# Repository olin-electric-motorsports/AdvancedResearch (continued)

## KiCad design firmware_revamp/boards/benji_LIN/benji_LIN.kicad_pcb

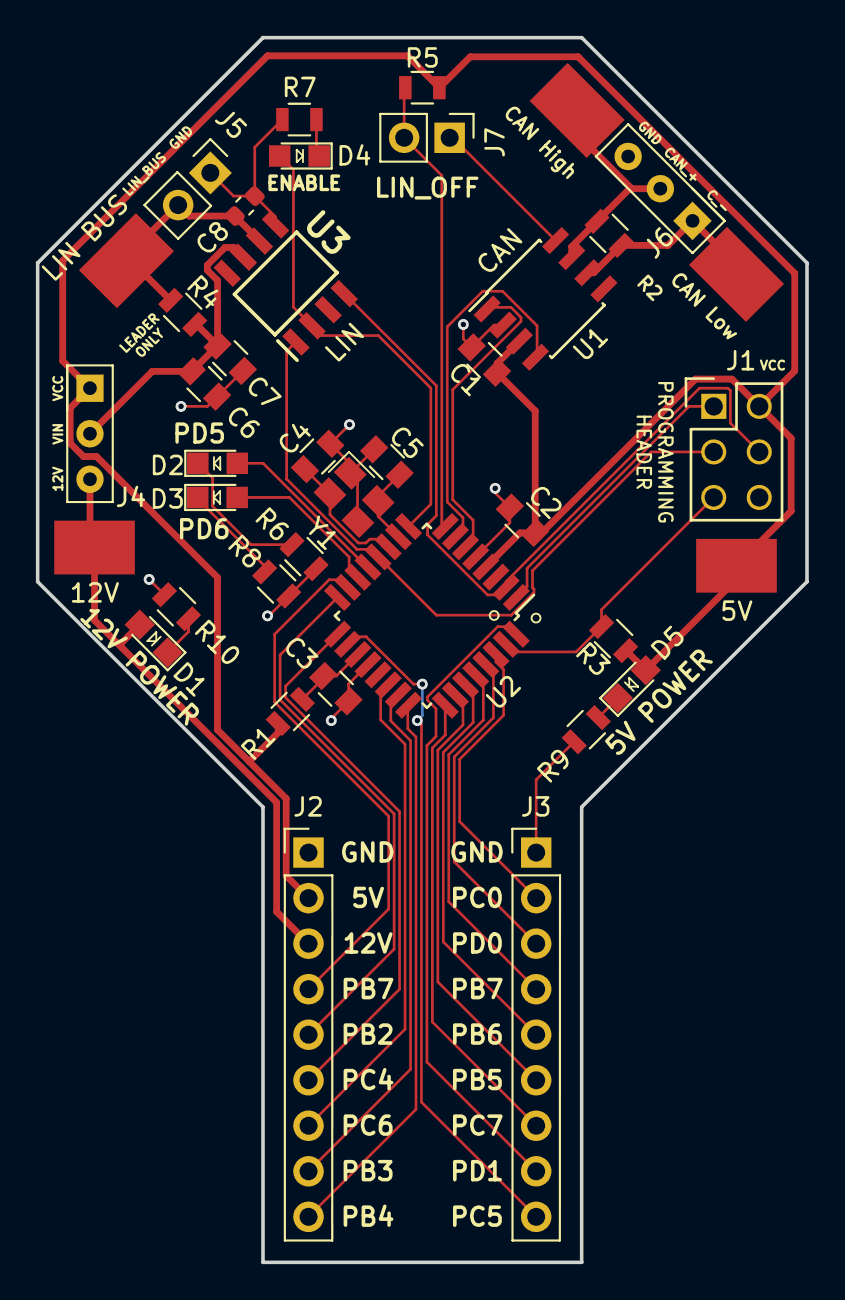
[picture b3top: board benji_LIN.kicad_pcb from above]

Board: 2 copper layers, 42.9 x 68.3 mm, 39 parts (0 on the bottom side), 39 nets.

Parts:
5V, 12V: Test_Point_SMD
C1, C2, C6, C7: C_0.1uF; C_0805_OEM
C3: C_100pF; C_0805_OEM
C4, C5: C_30pF; C_0805_OEM
C8: C_220pF; C_0603_1608Metric
CAN High: Test_Point_SMD
CAN Low: Test_Point_SMD
D1, D5: LED_0805_Amber; LED_0805_OEM
D2: LED_0805; LED_0805_OEM
D3: LED_0805_Red; LED_0805_OEM
D4: LIN_INDICATOR_LED; LED_0805_OEM
J1: CONN_02X03; Pin_Header_Straight_2x03
J2, J3: Conn_01x09; PinHeader_1x9_P2.54mm_Vertical
J4, J6: CONN_01X03; PinHeader_1x03_P2.54mm_Vertical
J5, J7: CONN_01x02; PinHeader_1x02_P2.54mm_Vertical
LIN BUS: Test_Point_SMD
R1: R_100; R_0805_OEM
R2: R_120_DNP; R_0805_OEM
R3: R_10K; R_0805_OEM
R4, R5, R6, R7, R8, R9: R_1K; R_0805_OEM
R10: R_2.2K; R_0805_OEM
U1: MCP2561-E_SN; SOIC-8_3.9x4.9mm_Pitch1.27mm_OEM
U2: ATMEGA16M1; TQFP-32_7x7mm_Pitch0.8mm
U3: TLIN1021DRQ1; SOIC127P600X175-8N
Y1: Crystal_SMD; Crystal_SMD_FA238

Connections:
/12V: 12V.1, D1.2, J2.3, J4.3
/CAN_+: CAN High.1, J6.2, R2.1, U1.7
/CAN_-: CAN Low.1, J6.1, R2.2, U1.6
/CAN_RX: U1.4, U2.7
/CAN_TX: U1.1, U2.6
/ENABLE: D4.2, U2.9, U3.2
/LEFT_DEBUG: D2.2, U2.13
/LIN_BUS: C8.1, J5.2, LIN BUS.1, R4.2, U3.6
/MISO: J1.1, U2.1
/MOSI: J1.4, U2.2, U3.4
/PB2: J2.5, U2.16
/PB3: J2.8, U2.23
/PB4: J2.9, U2.24
/PB5: J3.6, U2.26
/PB6: J3.5, U2.27
/PB7: J3.4, U2.28
/PC0: J3.2, U2.30
/PC4: J2.6, U2.17
/PC5: J3.9, U2.18
/PC6: J2.7, U2.22
/PC7: J3.7, U2.25
/PD0: J3.3, U2.29
/PD1: J3.8, U2.32
/PD7: J2.4, U2.15
/RESET: J1.5, R3.2, U2.31
/RIGHT_DEBUG: D3.2, U2.14
/RXLIN: J1.3, U2.12, U3.1
/VIN: C6.1, C7.1, J4.2, R4.1, U3.7
GND: C1.2, C2.2, C3.2, C4.2, C5.2, C6.2, C7.2, C8.2, J1.6, J2.1, J3.1, J5.1, J6.3, J7.1, R6.2, R7.2, R8.2, R9.2, R10.2, U1.2, U1.8, U2.5, U2.20, U3.5, Y1.2, Y1.4
unnamed: C3.1, R1.2, U2.19
unnamed: C4.1, U2.11, Y1.1
unnamed: C5.1, U2.10, Y1.3
unnamed: D1.1, R10.1
unnamed: D2.1, R6.1
unnamed: D3.1, R8.1
unnamed: D4.1, R7.1
unnamed: D5.1, R9.1
unnamed: J7.2, R5.1, U2.8
VCC: 5V.1, C1.1, C2.1, D5.2, J1.2, J2.2, J4.1, R1.1, R3.1, R5.2, U1.3, U2.4

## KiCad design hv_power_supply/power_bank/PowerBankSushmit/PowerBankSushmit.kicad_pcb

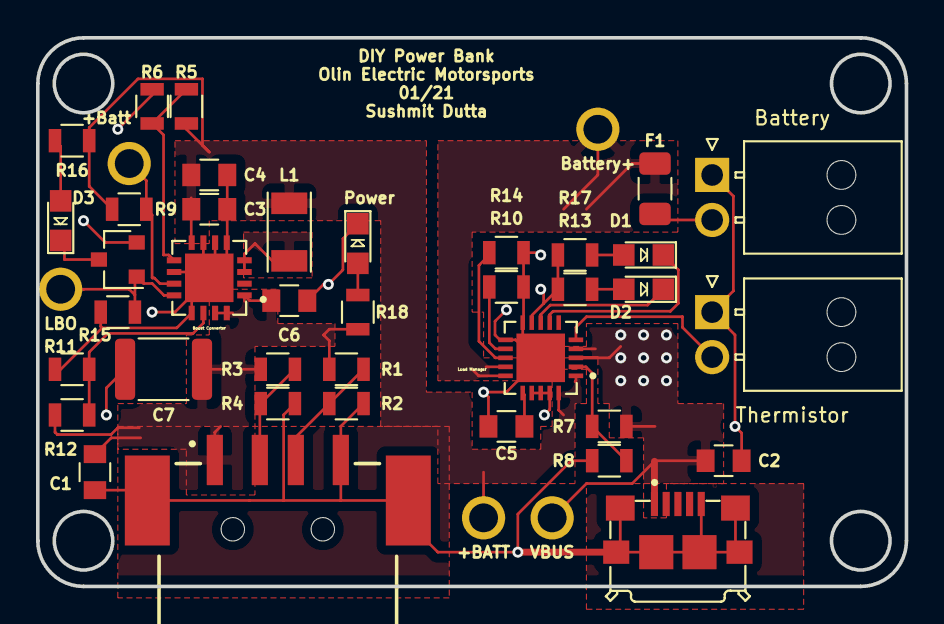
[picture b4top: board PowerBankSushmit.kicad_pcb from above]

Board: 2 copper layers, 48.3 x 30.5 mm, 43 parts (0 on the bottom side), 25 nets.

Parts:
+BATT: TP; tp_1.6mm
+Batt: TP; tp_1.6mm
Battery: NanoFit_RA_TH_02; NanoFit_Molex_1x02x2.50mm_Angled_OEM
Battery+: TP; tp_1.6mm
Boost Converter: TPS61090RSAR
C1, C2, C3, C4: C_10uF; C_0805_OEM
C5: C_10nF; C_0805_OEM
C6: C_2.2uF; C_0805_OEM
C7: C_100uF; C_1812_4532Metric
D1, D3: LED_0805; LED_0805_OEM
D2: LED_0805_Amber; LED_0805_OEM
F1: 1.5A_Fuse; Fuse_1206
J3: USB-A-S-X-X-SM2; SAMTEC_USB-A-S-X-X-SM2
L1: L_6.8uH; L_100uH_OEM
LBO: TP; tp_1.6mm
Load Manager: MCP73871T-2CCI_ML; MCP73871T
Power : LED_0805; LED_0805_OEM
Q1: SSM3K333R; SOT-23F
R1: R_75k; R_0805_OEM
R2, R4: R_49.9K; R_0805_OEM
R3: R_43k; R_0805_OEM
R5, R11: R_1.87M; R_0805_OEM
R6: R_340K; R_0805_OEM
R7: R_270K; R_0805_OEM
R8, R10: R_100K; R_0805_OEM
R9, R12: R_200K; R_0805_OEM
R13, R14, R16, R17, R18: R_1K; R_0805_OEM
R15: R_10K; R_0805_OEM
Thermistor: NanoFit_RA_TH_02; NanoFit_Molex_1x02x2.50mm_Angled_OEM
U1: USB-Micro-1981568-1; TE_1981568-1
VBUS: TP; tp_1.6mm

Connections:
+5V: Boost Converter.1, Boost Converter.15, Boost Converter.16, C1.1, C6.1, C7.1, J3.01, R1.1, R3.1, R11.1, R18.1
+BATT: +BATT.1, Boost Converter.8, C3.1, C4.1, L1.1, Load Manager.1, Load Manager.20, R5.1, R9.2, R16.1
/16K_Thermistor: Load Manager.5, Thermistor.2
/Battery+: Battery+.1, F1.2, Load Manager.14, Load Manager.15
GND: Battery.1, Boost Converter.5, Boost Converter.6, Boost Converter.7, Boost Converter.10, Boost Converter.13, Boost Converter.17, C1.2, C2.2, C3.2, C4.2, C5.2, C6.2, C7.2, J3.04, J3.S1, J3.S2, Load Manager.10, Load Manager.11, Load Manager.21, Power.1, Q1.2, R2.2, R4.2, R6.2, R8.2, R10.2, R12.2, R14.2, R15.2, Thermistor.1, U1.5, U1.6, U1.7, U1.8, U1.9, U1.10, U1.11
unnamed: C5.1, Load Manager.16
unnamed: D1.1, Load Manager.7
unnamed: D1.2, R17.1
unnamed: D2.1, Load Manager.8
unnamed: D2.2, R13.2
unnamed: D3.1, Q1.3
unnamed: D3.2, R16.2
unnamed: Power.2, R18.2
unnamed: Battery.2, F1.1
unnamed: J3.02, R3.2, R4.1
unnamed: J3.03, R1.2, R2.1
unnamed: Boost Converter.3, Boost Converter.4, L1.2
unnamed: Boost Converter.12, LBO.1, Q1.1, R15.1
unnamed: Boost Converter.9, R5.2, R6.1
unnamed: Load Manager.2, R7.2, R8.1
unnamed: +Batt.1, Boost Converter.11, R9.1
unnamed: Load Manager.12, R10.1
unnamed: Boost Converter.14, R11.2, R12.1
unnamed: Load Manager.13, R14.1
VBUS: C2.1, Load Manager.3, Load Manager.4, Load Manager.9, Load Manager.17, Load Manager.18, Load Manager.19, R7.1, R13.1, R17.2, U1.1, VBUS.1

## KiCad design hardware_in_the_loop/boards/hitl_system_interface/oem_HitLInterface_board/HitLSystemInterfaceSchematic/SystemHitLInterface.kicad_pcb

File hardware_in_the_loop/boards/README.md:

# Boards

This is where the KiCAD files for the Hardware in the Loop project live.

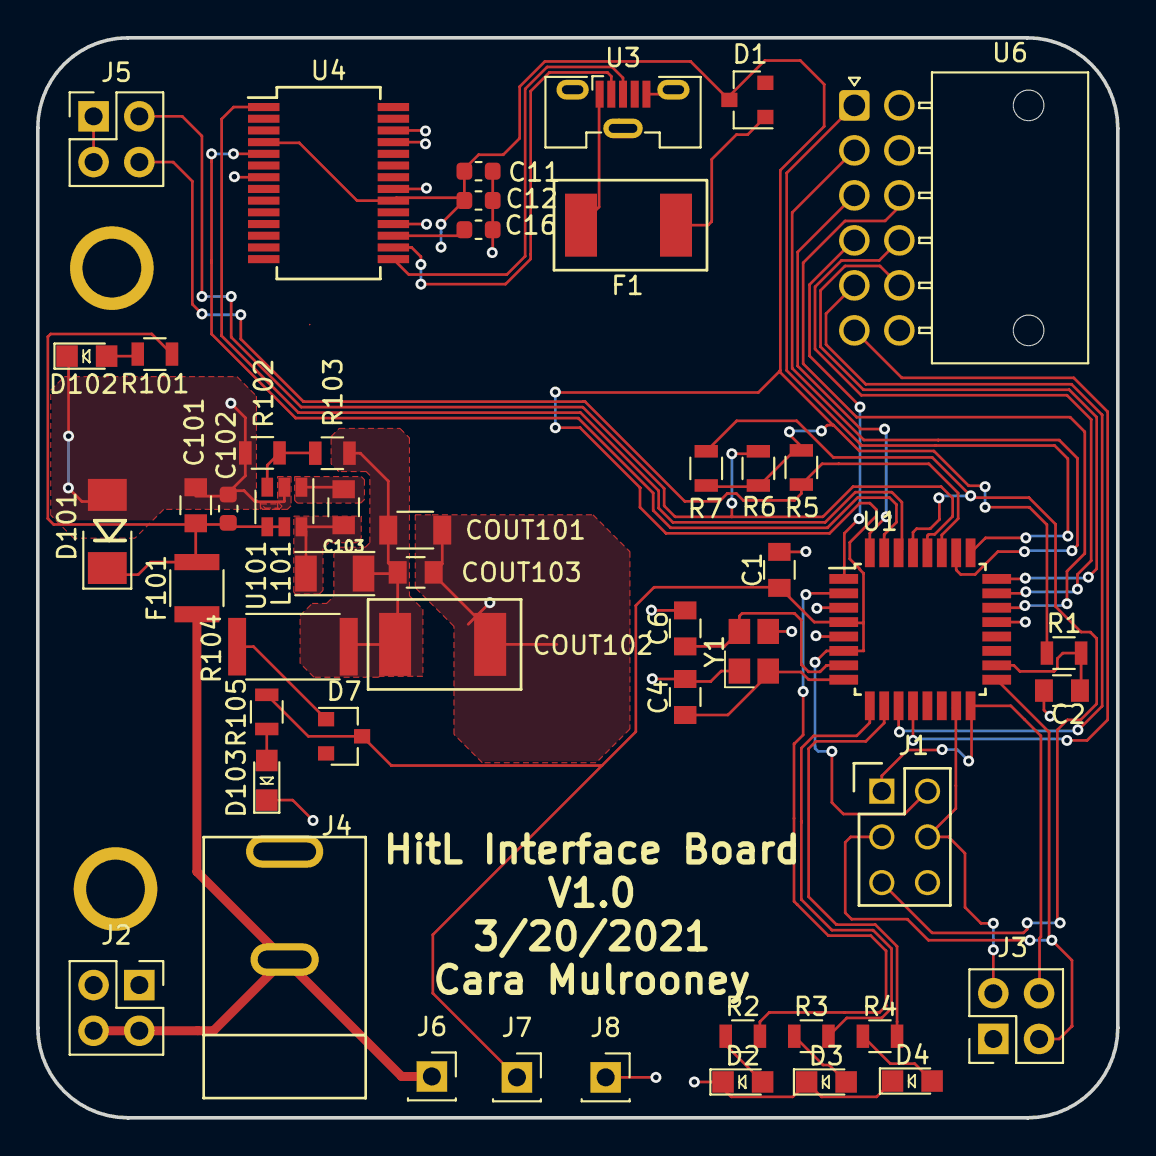
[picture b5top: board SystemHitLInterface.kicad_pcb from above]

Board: 2 copper layers, 60.0 x 60.0 mm, 50 parts (0 on the bottom side), 42 nets.

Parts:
C1, C101, C103: C_0.1uF; C_0805_OEM
C2: C_100pF; C_0805_OEM
C4, C6: C_30pF; C_0805_OEM
C11: C_4.7uF; C_0603_1608Metric
C12, C16: C_100nF; C_0603_1608Metric
C102: C_2.2uF; C_0603_1608Metric
COUT101: C_22uF; C_1206_OEM
COUT102: C_33uF; Fuse_1812
COUT103: C_47uF; C_0805_OEM
D1, D7: BAS40-00; SOT-23
D2, D3, D4, D102, D103: LED_0805; LED_0805_OEM
D101: D_Zener_18V; DO-214AA
F1: 200mA_Fuse; Fuse_1812
F101: F_500mA_16V; Fuse_1210
J1: CONN_02X03; Pin_Header_Straight_2x03
J2, J3, J5: Conn_01x04_Female; PinSocket_2x02_P2.54mm_Vertical
J4: Barrel_Jack; barrel_jack_PJ-037A
J6, J7, J8: Conn_01x01_Female; PinSocket_1x01_P2.54mm_Vertical
L101: L_100uH; L_100uH_OEM
R1: R_100; R_0805_OEM
R2, R3, R4, R105: R_200; R_0805_OEM
R5, R6, R7: R_10K; R_0805_OEM
R101: R_1K; R_0805_OEM
R102: R_25K; R_0805_OEM
R103: R_100K; R_0805_OEM
R104: R_0_2512; R_2512_OEM
U1: ATmega328P-AU; TQFP-32_7x7mm_P0.8mm
U3: USB_MicroB; USB_Micro-B_Molex-105133-0031
U4: FT232RL; SSOP-28_5.3x10.2mm_P0.65mm
U6: NanoFit_RA_TH_12; NanoFit_RA_12
U101: TPS560430YF; SOT-23-6_OEM
Y1: Crystal_SMD; Crystal_SMD_FA238

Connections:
/12V: F101.1, J2.3, J2.4, J4.2, J6.1
/AI2: U1.22, U6.9
/AI3: U1.23, U6.10
/AI4: U1.24, U6.11
/D1: U1.25, U6.1
/D2: U1.26, U6.2
/D3: U1.32, U6.3
/D4: U1.1, U6.4
/D5: U1.11, U6.5
/D6: U1.12, U6.6
/MISO: J1.1, J3.4, U1.16
/MOSI: J1.4, J3.3, U1.15
/RESET: J1.5, R7.2, U1.29
/RXD: U1.30, U4.1
/SCK: J1.3, J3.2, U1.17
/SCL: J5.3, R6.2, U1.28
/SDA: J5.4, R5.2, U1.27
/TXD: U1.31, U4.5
/USBDM: U3.2, U4.16
/USBDP: U3.3, U4.15
GND: C1.2, C2.2, C4.2, C6.2, C11.1, C12.1, C16.2, C101.2, C102.2, COUT101.2, COUT102.2, COUT103.2, D2.1, D3.1, D4.1, D101.2, D102.1, D103.1, J1.6, J2.1, J2.2, J4.1, J5.1, J5.2, J8.1, R102.2, U1.3, U1.5, U1.21, U3.5, U3.6, U4.7, U4.18, U4.21, U4.25, U4.26, U101.2, Y1.2, Y1.4
unnamed: C2.1, R1.2, U1.18
unnamed: C4.1, U1.8, Y1.1
unnamed: C6.1, U1.7, Y1.3
unnamed: C16.1, U4.17
unnamed: C101.1, C102.1, D101.1, F101.2, R101.1, U101.4, U101.5
unnamed: C103.1, U101.1
unnamed: C103.2, L101.1, U101.6
unnamed: COUT101.1, COUT102.1, COUT103.1, L101.2, R103.1, R104.1
unnamed: D1.1, F1.2
unnamed: D2.2, R2.1
unnamed: D3.2, R3.1
unnamed: D4.2, R4.1
unnamed: D7.1, R104.2
unnamed: D102.2, R101.2
unnamed: D103.2, R105.2
unnamed: F1.1, U3.1
unnamed: R2.2, U1.2
unnamed: R3.2, U1.9
unnamed: R4.2, U1.10
unnamed: R102.1, R103.2, U101.3
VCC: C1.1, C11.2, C12.2, D1.3, D7.3, J1.2, J7.1, R1.1, R5.1, R6.1, R7.1, R105.1, U1.4, U1.6, U4.4, U4.20

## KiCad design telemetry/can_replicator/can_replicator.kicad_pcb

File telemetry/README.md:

# Telemetry

This project will allow wireless communication between the car's communications bus and the pit.

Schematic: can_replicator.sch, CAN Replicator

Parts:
C1, C2: C_0.1uF; C_0805_OEM; MPN 478-3352-1-ND
C3: C_100pF; C_0805_OEM; MPN 732-7852-1-ND
C4, C5: C_30pF; C_0805_OEM; MPN 1276-1130-1-ND
C6: C_10nF; C_0805_OEM; MPN 1276-1015-1-ND
C7, C9: C_100nF; C_0603_1608Metric; MPN 1276-6717-1-ND
C8: C_4.7uF; C_0603_1608Metric; MPN 1276-1045-1-ND
D1, D2: LED_0805_Amber; LED_0805_OEM; MPN L71517CT-ND
D3, D4, D5, D6: LED_0805; LED_0805_OEM; MPN 475-1410-1-ND
D7: BAT400D-7-F; SOT-23-3_OEM
D8: D_Zener_5.6V; D_5.6V_Zener; MPN 3SMBJ5919B-TP
F1: F_500mA_16V; Fuse_1210; MPN 507-1786-1-ND
J1: CONN_02X03; Pin_Header_Straight_2x03; MPN 609-3234-ND
J2: MM_M_VT_20; micromatch_female_ra_20; MPN 2-215464-0
J3, J4: CONN_01X03; PinHeader_1x03_P2.54mm_Vertical; MPN 855-M20-9990346
R1: R_100; R_0805_OEM; MPN RNCP0805FTD100RCT-ND
R2, R12: R_120; R_0805_OEM; MPN 667-ERJ-6ENF1200V
R3: R_10K; R_0805_OEM; MPN CRS0805-FX-1002ELFCT-ND
R4, R5, R6, R7, R8, R9: R_200; R_0805_OEM; MPN RMCF0805JT200RCT-ND
R10, R11: R_500; R_0805_OEM
TP1, TP2: Test_Point_SMD
U1: MCP2561-E_SN; SOIC-8_3.9x4.9mm_Pitch1.27mm_OEM; MPN MCP2561-E/SN-ND
U2: ATMEGA16M1; TQFP-32_7x7mm_Pitch0.8mm; MPN ATMEGA16M1-AU-ND
U3: USB_MicroB; USB_Micro-B_Molex-105017-0001; MPN WM1399CT-ND
U4: FT232RL; SSOP-28_5.3x10.2mm_P0.65mm; Part Number (DK) 768-1007-1-ND
Y1: Crystal_SMD; Crystal_SMD_FA238; MPN 887-1125-1-ND

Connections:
+5V: C1.1, C2.1, C6.2, C7.1, C8.1, D1.2 (A), D2.2 (A), D3.2 (A), D7.1 (K), D8.1 (K), J1.2, R1.1, R3.1, U1.3 (VDD), U2.4 (VCC), U4.4 (VCCIO), U4.19 (~RESET~), U4.20 (VCC)
/CAN_+: J2.3, R2.1, R12.1, U1.7 (CANH)
/CAN_-: J2.4, J3.2, J4.2, U1.6 (CANL)
/CAN_RX: U1.4 (RXD), U2.7 ((PCINT11/T1/ICP1B/RXCAN)PC3)
/CAN_TX: U1.1 (TXD), U2.6 ((PCINT10/T0/TXCAN)PC2)
/DBG1: D4.2 (A), U2.22 ((PCINT14/ADC10/ACMP1)PC6)
/DBG2: D5.2 (A), U2.23 ((PCINT3/AMP0-)PB3)
/DBG3: D6.2 (A), U2.24 ((PCINT4/AMP0+)PB4)
/MISO: J1.1, U2.1 ((PCINT18/PSCIN2/OC1A/MISO_A)PD2)
/MOSI: J1.4, R10.1, U2.2 ((PCINT19/TXD/TXLIN/OC0A/~SS~/MOSI_A)PD3)
/RESET: J1.5, R3.2, U2.31 ((PCINT24/OCD/~RESET~)PE0)
/RXLED: R7.1, U4.22 (CBUS1)
/SCK: J1.3, R11.1, U2.12 ((PCINT20/ADC1/RXD/RXLIN/ICP1A/SCK_A)PD4)
/TXLED: R8.1, U4.23 (CBUS0)
/UART_RXD: R10.2, U4.5 (RXD)
/UART_TXD: R11.2, U4.1 (TXD)
/USBD+: U3.3 (D+), U4.15 (USBD+)
/USBD-: U3.2 (D-), U4.16 (USBD-)
GND: C1.2, C2.2, C3.2, C4.2, C5.2, C6.1, C7.2, C8.2, C9.2, D8.2 (A), J1.6, J2.1, J2.5, J2.6, J2.7, J2.8, J2.9, J2.10, J2.11, J2.12, J2.13, J2.14, J2.15, J2.16, J2.17, J2.18, J2.19, J2.20, R4.1, R5.1, R6.1, R9.1, TP1.1, U1.2 (VSS), U1.8 (STBY), U2.5 (GND), U2.20 (AGND), U3.5 (GND), U4.7 (GND), U4.18 (GND), U4.21 (GND), U4.25 (AGND), U4.26 (TEST), Y1.2, Y1.4
unnamed: C3.1, R1.2, U2.19 (AVCC)
unnamed: C4.1, U2.11 ((PCINT26/ADC0/XTAL2)PE2), Y1.1
unnamed: C5.1, U2.10 ((PCINT25/OC0B/XTAL1)PE1), Y1.3
unnamed: C9.1, U4.17 (3V3OUT)
unnamed: D1.1 (K), R7.2
unnamed: D2.1 (K), R8.2
unnamed: D3.1 (K), R9.2
unnamed: D4.1 (K), R4.2
unnamed: D5.1 (K), R5.2
unnamed: D6.1 (K), R6.2
unnamed: D7.2 (A), F1.1
unnamed: F1.2, TP2.1, U3.1 (VBUS)
unnamed: J3.3, R2.2
unnamed: J4.3, R12.2

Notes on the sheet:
ATMEGA 16M1
16 MHz CRYSTAL
USB + POWER
+4.4V - +5.25V
USB RX
USB TX
POWER
STATUS LEDS
CAN TRANSCEIVER
CONNECTOR
16M1 PROGRAMMING HEADER
JUMPERS FOR TERMINATING RESISTORS

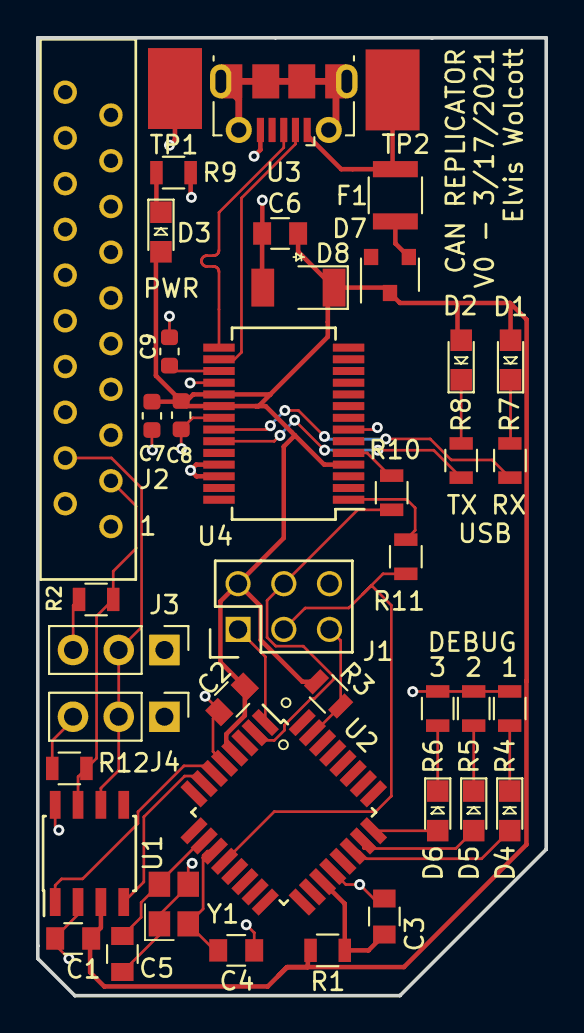
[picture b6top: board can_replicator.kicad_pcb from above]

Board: 2 copper layers, 28.2 x 53.2 mm, 41 parts (0 on the bottom side), 33 nets.

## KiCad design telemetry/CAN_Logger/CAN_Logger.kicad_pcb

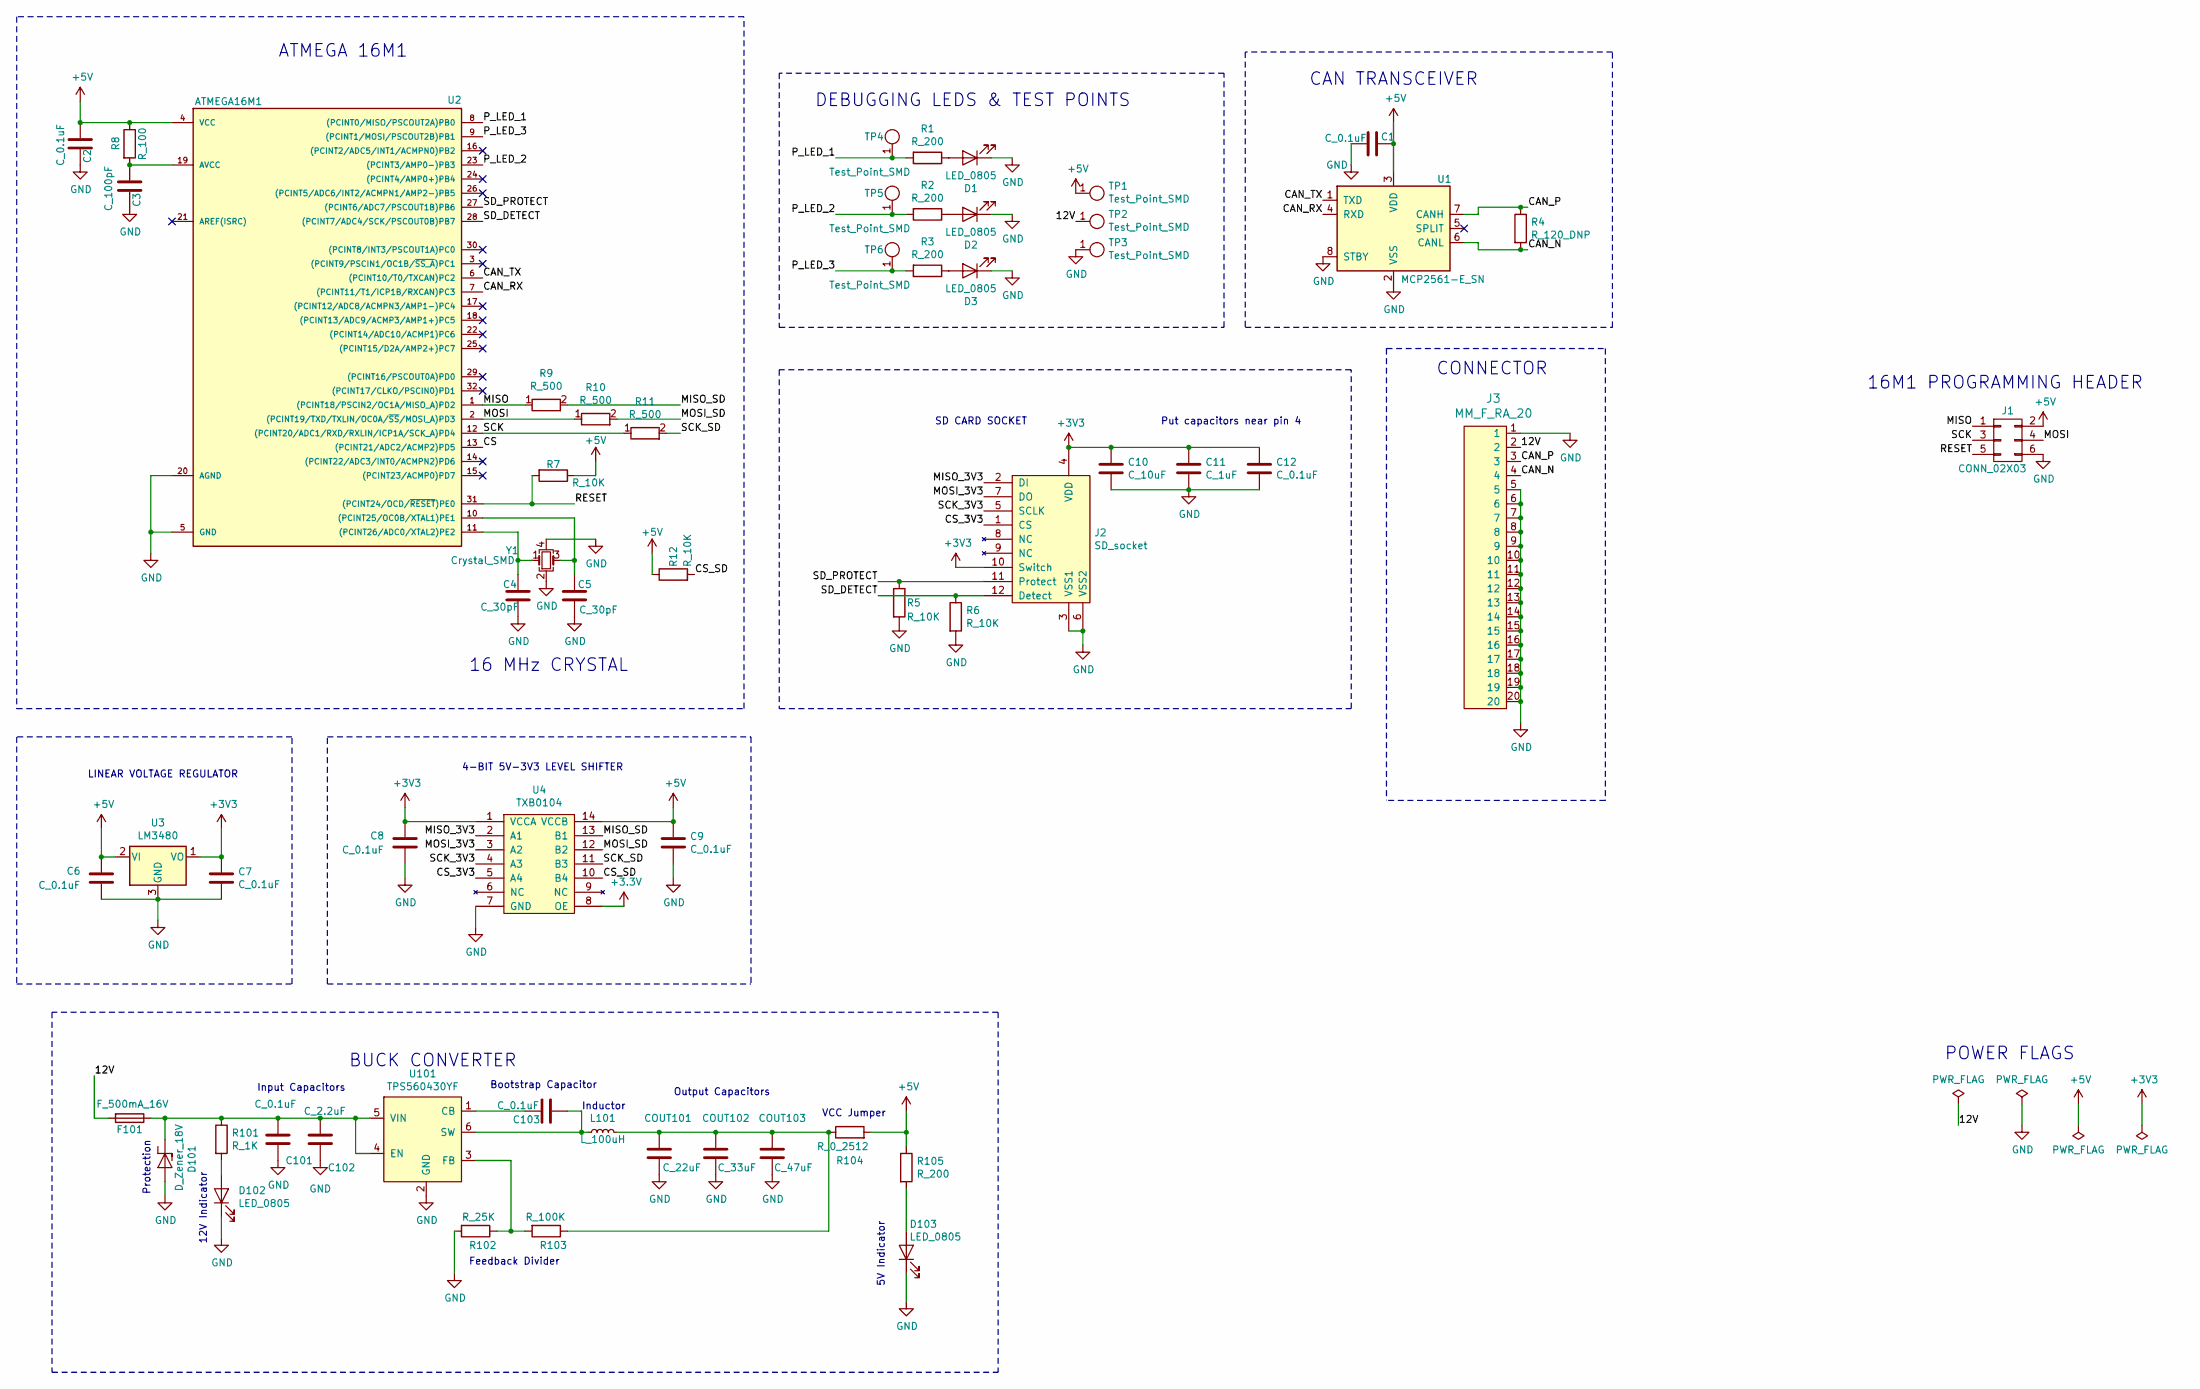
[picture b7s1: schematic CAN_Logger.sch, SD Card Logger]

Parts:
C1, C2, C6, C7, C8, C9, C12, C101, C103: C_0.1uF; C_0805_OEM; MPN 478-3352-1-ND
C3: C_100pF; C_0805_OEM; MPN 732-7852-1-ND
C4, C5: C_30pF; C_0805_OEM; MPN 1276-1130-1-ND
C10: C_10uF; C_0805_OEM; MPN 1276-1052-1-ND
C11: C_1uF; C_0805_OEM
C102: C_2.2uF; C_0603_1608Metric
COUT101: C_22uF; C_1206_OEM; MPN 445-11693-1-ND
COUT102: C_33uF; Fuse_1812; MPN 445-3924-1-ND
COUT103: C_47uF; C_0805_OEM; MPN 1276-6467-1-ND
D1, D2, D3, D102, D103: LED_0805; LED_0805_OEM; MPN 475-1410-1-ND
D101: D_Zener_18V; DO-214AA; MPN SMBJ5355B-TPMSCT-ND
F101: F_500mA_16V; Fuse_1210; MPN 507-1786-1-ND
J1: CONN_02X03; Pin_Header_Straight_2x03; MPN 609-3234-ND
J2: SD_socket; sd_socket_molex_5009980900; MPN WM24032CT-ND
J3: MM_F_RA_20; micromatch_female_ra_20; MPN 2-338070-0
L101: L_100uH; L_100uH_OEM; MPN 445-15759-1-ND
R1, R2, R3, R105: R_200; R_0805_OEM; MPN RMCF0805JT200RCT-ND
R4: R_120_DNP; R_0805_OEM; MPN 667-ERJ-6ENF1200V
R5, R6, R7, R12: R_10K; R_0805_OEM; MPN CRS0805-FX-1002ELFCT-ND
R8: R_100; R_0805_OEM; MPN RNCP0805FTD100RCT-ND
R9, R10, R11: R_500; R_0805_OEM
R101: R_1K; R_0805_OEM; MPN RNCP0805FTD1K00CT-ND
R102: R_25K; R_0805_OEM; MPN A124124CT-ND
R103: R_100K; R_0805_OEM; MPN P100KCCT-ND
R104: R_0_2512; R_2512_OEM; MPN A121322CT-ND
TP1, TP2, TP3, TP4, TP5, TP6: Test_Point_SMD
U1: MCP2561-E_SN; SOIC-8_3.9x4.9mm_Pitch1.27mm_OEM; MPN MCP2561-E/SN-ND
U2: ATMEGA16M1; TQFP-32_7x7mm_Pitch0.8mm; MPN ATMEGA16M1-AU-ND
U3: LM3480; SOT-23; MPN LM3480IM3-3.3CT-ND
U4: TXB0104; TSSOP-14_4.4x5mm_P0.65mm; MPN 296-21929-1-ND
U101: TPS560430YF; SOT-23-6_OEM; MPN TPS560430YFDBVR-ND
Y1: Crystal_SMD; Crystal_SMD_FA238; MPN 887-1125-1-ND

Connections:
+5V: C1.1, C2.1, C6.1, C9.1, J1.2, R7.1, R8.1, R12.1, R104.2, R105.1, TP1.1, U1.3 (VDD), U2.4 (VCC), U3.2 (VI), U4.14 (VCCB)
/12V: F101.2, J3.2, TP2.1
/CAN_N: J3.4, R4.2, U1.6 (CANL)
/CAN_P: J3.3, R4.1, U1.7 (CANH)
/CAN_RX: U1.4 (RXD), U2.7 ((PCINT11/T1/ICP1B/RXCAN)PC3)
/CAN_TX: U1.1 (TXD), U2.6 ((PCINT10/T0/TXCAN)PC2)
/CS_3V3: J2.1 (CS), U4.5 (A4)
/MISO: J1.1, R9.1, U2.1 ((PCINT18/PSCIN2/OC1A/MISO_A)PD2)
/MISO_3V3: J2.2 (DI), U4.2 (A1)
/MISO_SD: R9.2, U4.13 (B1)
/MOSI: J1.4, R10.1, U2.2 ((PCINT19/TXD/TXLIN/OC0A/~SS~/MOSI_A)PD3)
/MOSI_3V3: J2.7 (DO), U4.3 (A2)
/MOSI_SD: R10.2, U4.12 (B2)
/P_LED_1: R1.2, TP4.1, U2.8 ((PCINT0/MISO/PSCOUT2A)PB0)
/P_LED_2: R2.2, TP5.1, U2.23 ((PCINT3/AMP0-)PB3)
/P_LED_3: R3.2, TP6.1, U2.9 ((PCINT1/MOSI/PSCOUT2B)PB1)
/RESET: J1.5, R7.2, U2.31 ((PCINT24/OCD/~RESET~)PE0)
/SCK: J1.3, R11.1, U2.12 ((PCINT20/ADC1/RXD/RXLIN/ICP1A/SCK_A)PD4)
/SCK_3V3: J2.5 (SCLK), U4.4 (A3)
/SCK_SD: R11.2, U4.11 (B3)
/SD_DETECT: J2.12 (Detect), R6.1, U2.28 ((PCINT7/ADC4/SCK/PSCOUT0B)PB7)
/SD_PROTECT: J2.11 (Protect), R5.1, U2.27 ((PCINT6/ADC7/PSCOUT1B)PB6)
GND: C1.2, C2.2, C3.2, C4.2, C5.2, C6.2, C7.2, C8.2, C9.2, C10.2, C11.2, C12.2, C101.2, C102.2, COUT101.2, COUT102.2, COUT103.2, D1.1 (K), D2.1 (K), D3.1 (K), D101.2 (A), D102.1 (K), D103.1 (K), J1.6, J2.3 (VSS1), J2.6 (VSS2), J3.1, J3.5, J3.6, J3.7, J3.8, J3.9, J3.10, J3.11, J3.12, J3.13, J3.14, J3.15, J3.16, J3.17, J3.18, J3.19, J3.20, R5.2, R6.2, R102.2, TP3.1, U1.2 (VSS), U1.8 (STBY), U2.5 (GND), U2.20 (AGND), U3.3 (GND), U4.7 (GND), U101.2 (GND), Y1.2, Y1.4
unnamed: C3.1, R8.2, U2.19 (AVCC)
unnamed: C4.1, U2.11 ((PCINT26/ADC0/XTAL2)PE2), Y1.1
unnamed: C5.1, U2.10 ((PCINT25/OC0B/XTAL1)PE1), Y1.3
unnamed: C101.1, C102.1, D101.1 (K), F101.1, R101.1, U101.4 (EN), U101.5 (VIN)
unnamed: C103.1, U101.1 (CB)
unnamed: C103.2, L101.1, U101.6 (SW)
unnamed: COUT101.1, COUT102.1, COUT103.1, L101.2, R103.1, R104.1
unnamed: D1.2 (A), R1.1
unnamed: D2.2 (A), R2.1
unnamed: D3.2 (A), R3.1
unnamed: D102.2 (A), R101.2
unnamed: D103.2 (A), R105.2
unnamed: R102.1, R103.2, U101.3 (FB)

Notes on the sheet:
POWER FLAGS
16M1 PROGRAMMING HEADER
LINEAR VOLTAGE REGULATOR
4-BIT 5V-3V3 LEVEL SHIFTER
SD CARD SOCKET
Put capacitors near pin 4
CAN TRANSCEIVER
16 MHz CRYSTAL
ATMEGA 16M1
DEBUGGING LEDS & TEST POINTS
BUCK CONVERTER
Input Capacitors
12V Indicator
Protection
Feedback Divider
Output Capacitors
VCC Jumper
5V Indicator
Inductor
Bootstrap Capacitor
CONNECTOR

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
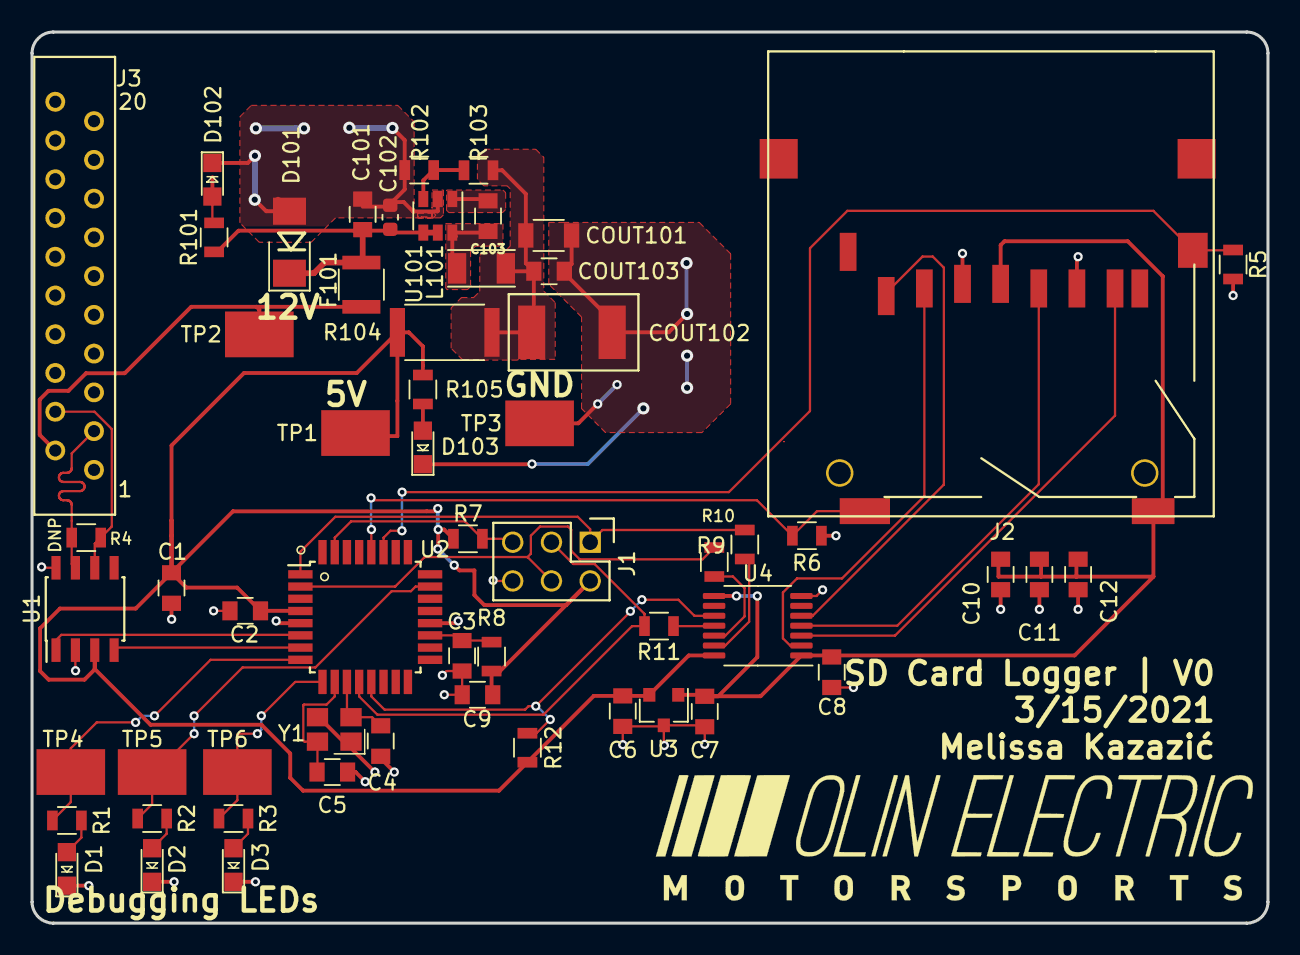
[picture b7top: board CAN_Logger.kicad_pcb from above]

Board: 2 copper layers, 81.0 x 58.4 mm, 58 parts (0 on the bottom side), 38 nets.

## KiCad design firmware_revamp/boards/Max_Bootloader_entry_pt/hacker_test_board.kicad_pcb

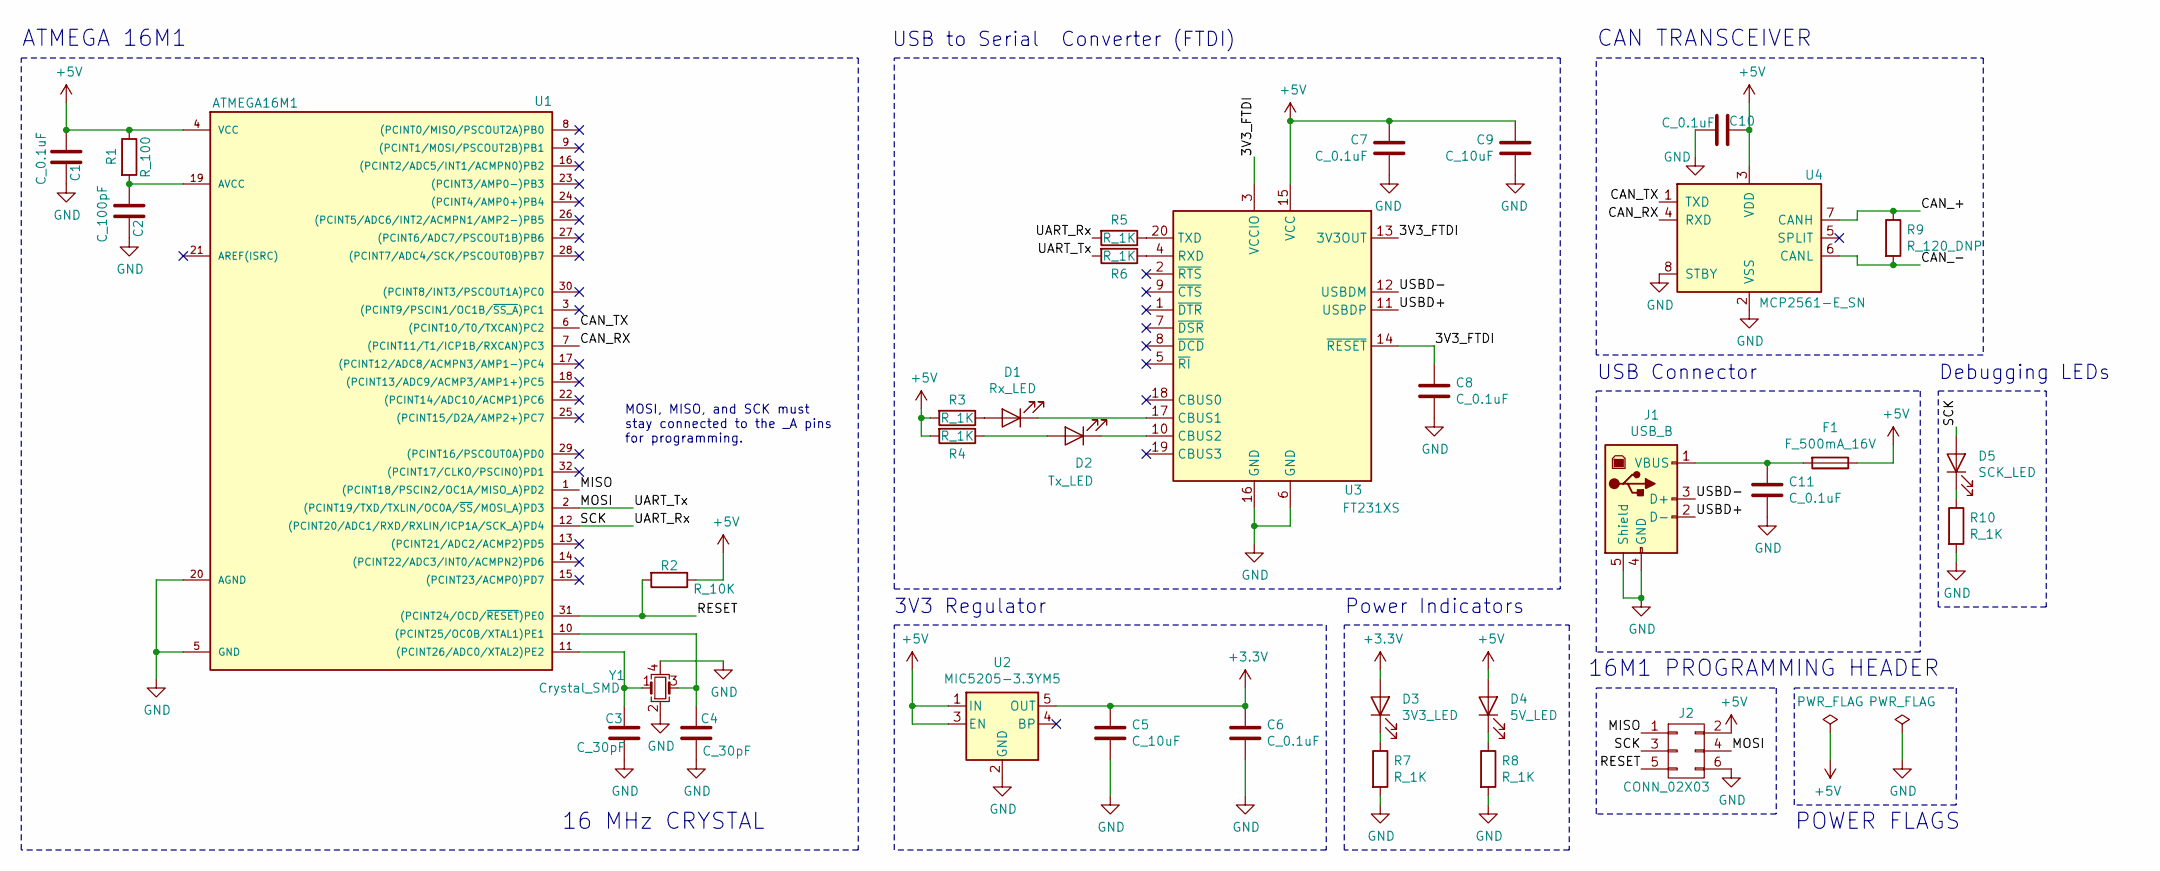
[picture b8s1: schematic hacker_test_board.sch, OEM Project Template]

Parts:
C1, C6, C7, C8, C10, C11: C_0.1uF; C_0805_OEM; MPN 478-3352-1-ND
C2: C_100pF; C_0805_OEM; MPN 732-7852-1-ND
C3, C4: C_30pF; C_0805_OEM; MPN 1276-1130-1-ND
C5, C9: C_10uF; C_0805_OEM; MPN 1276-1052-1-ND
D1: Rx_LED; LED_0805_OEM; MPN 475-1410-1-ND
D2: Tx_LED; LED_0805_OEM; MPN 475-1410-1-ND
D3: 3V3_LED; LED_0805_OEM; MPN 475-1410-1-ND
D4: 5V_LED; LED_0805_OEM; MPN 475-1410-1-ND
D5: SCK_LED; LED_0805_OEM; MPN 475-1410-1-ND
F1: F_500mA_16V; Fuse_1210; MPN 507-1786-1-ND
J1: USB_B; USB_B_Lumberg_2411_02_Horizontal
J2: CONN_02X03; Pin_Header_Straight_2x03; MPN 609-3234-ND
R1: R_100; R_0805_OEM; MPN RNCP0805FTD100RCT-ND
R2: R_10K; R_0805_OEM; MPN CRS0805-FX-1002ELFCT-ND
R3, R4, R5, R6, R7, R8, R10: R_1K; R_0805_OEM; MPN RNCP0805FTD1K00CT-ND
R9: R_120_DNP; R_0805_OEM; MPN 667-ERJ-6ENF1200V
U1: ATMEGA16M1; TQFP-32_7x7mm_Pitch0.8mm; MPN ATMEGA16M1-AU-ND
U2: MIC5205-3.3YM5; SOT-23-5
U3: FT231XS; SSOP-20_3.9x8.7mm_P0.635mm
U4: MCP2561-E_SN; SOIC-8_3.9x4.9mm_Pitch1.27mm_OEM; MPN MCP2561-E/SN-ND
Y1: Crystal_SMD; Crystal_SMD_FA238; MPN 887-1125-1-ND

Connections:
+3V3: C5.1, C6.1, D3.2 (A), U2.5 (OUT)
+5V: C1.1, C7.1, C9.1, C10.1, D4.2 (A), F1.1, J2.2, R1.1, R2.1, R3.2, R4.2, U1.4 (VCC), U2.1 (IN), U2.3 (EN), U3.15 (VCC), U4.3 (VDD)
/3V3_FTDI: C8.1, U3.3 (VCCIO), U3.13 (3V3OUT), U3.14 (~RESET)
/CAN_+: R9.1, U4.7 (CANH)
/CAN_-: R9.2, U4.6 (CANL)
/CAN_RX: U1.7 ((PCINT11/T1/ICP1B/RXCAN)PC3), U4.4 (RXD)
/CAN_TX: U1.6 ((PCINT10/T0/TXCAN)PC2), U4.1 (TXD)
/MISO: J2.1, U1.1 ((PCINT18/PSCIN2/OC1A/MISO_A)PD2)
/MOSI: J2.4, R6.2, U1.2 ((PCINT19/TXD/TXLIN/OC0A/~SS~/MOSI_A)PD3)
/RESET: J2.5, R2.2, U1.31 ((PCINT24/OCD/~RESET~)PE0)
/SCK: D5.2 (A), J2.3, R5.2, U1.12 ((PCINT20/ADC1/RXD/RXLIN/ICP1A/SCK_A)PD4)
/USBD+: J1.2 (D-), U3.11 (USBDP)
/USBD-: J1.3 (D+), U3.12 (USBDM)
GND: C1.2, C2.2, C3.2, C4.2, C5.2, C6.2, C7.2, C8.2, C9.2, C10.2, C11.2, J1.4 (GND), J1.5 (Shield), J2.6, R7.2, R8.2, R10.2, U1.5 (GND), U1.20 (AGND), U2.2 (GND), U3.6 (GND), U3.16 (GND), U4.2 (VSS), U4.8 (STBY), Y1.2, Y1.4
unnamed: C2.1, R1.2, U1.19 (AVCC)
unnamed: C3.1, U1.11 ((PCINT26/ADC0/XTAL2)PE2), Y1.1
unnamed: C4.1, U1.10 ((PCINT25/OC0B/XTAL1)PE1), Y1.3
unnamed: C11.1, F1.2, J1.1 (VBUS)
unnamed: D1.1 (K), U3.17 (CBUS1)
unnamed: D1.2 (A), R3.1
unnamed: D2.1 (K), U3.10 (CBUS2)
unnamed: D2.2 (A), R4.1
unnamed: D3.1 (K), R7.1
unnamed: D4.1 (K), R8.1
unnamed: D5.1 (K), R10.1
unnamed: R5.1, U3.20 (TXD)
unnamed: R6.1, U3.4 (RXD)

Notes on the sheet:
ATMEGA 16M1
16 MHz CRYSTAL
USB Connector
3V3 Regulator
USB to Serial Converter (FTDI)
CAN TRANSCEIVER
MOSI, MISO, and SCK must stay connected to the _A pins for programming.
POWER FLAGS
16M1 PROGRAMMING HEADER
Power Indicators
Debugging LEDs

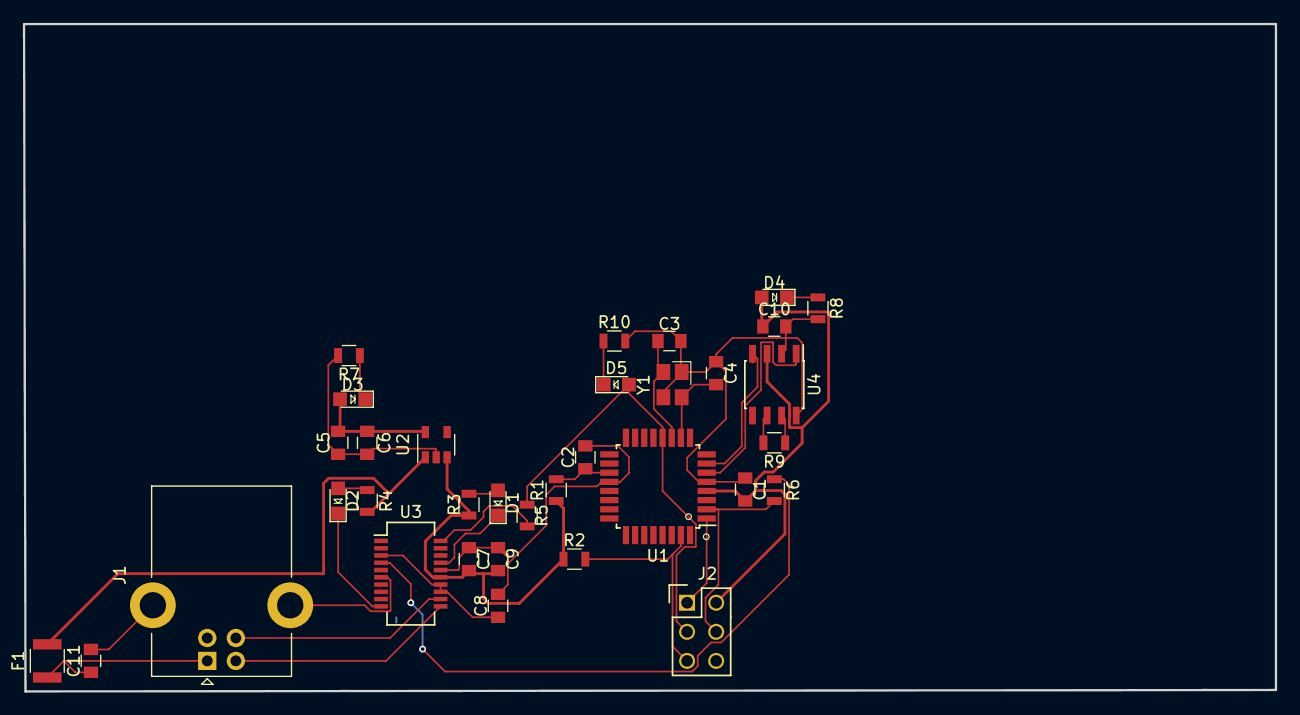
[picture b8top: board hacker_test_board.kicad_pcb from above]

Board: 2 copper layers, 109.3 x 58.3 mm, 34 parts (0 on the bottom side), 27 nets.
